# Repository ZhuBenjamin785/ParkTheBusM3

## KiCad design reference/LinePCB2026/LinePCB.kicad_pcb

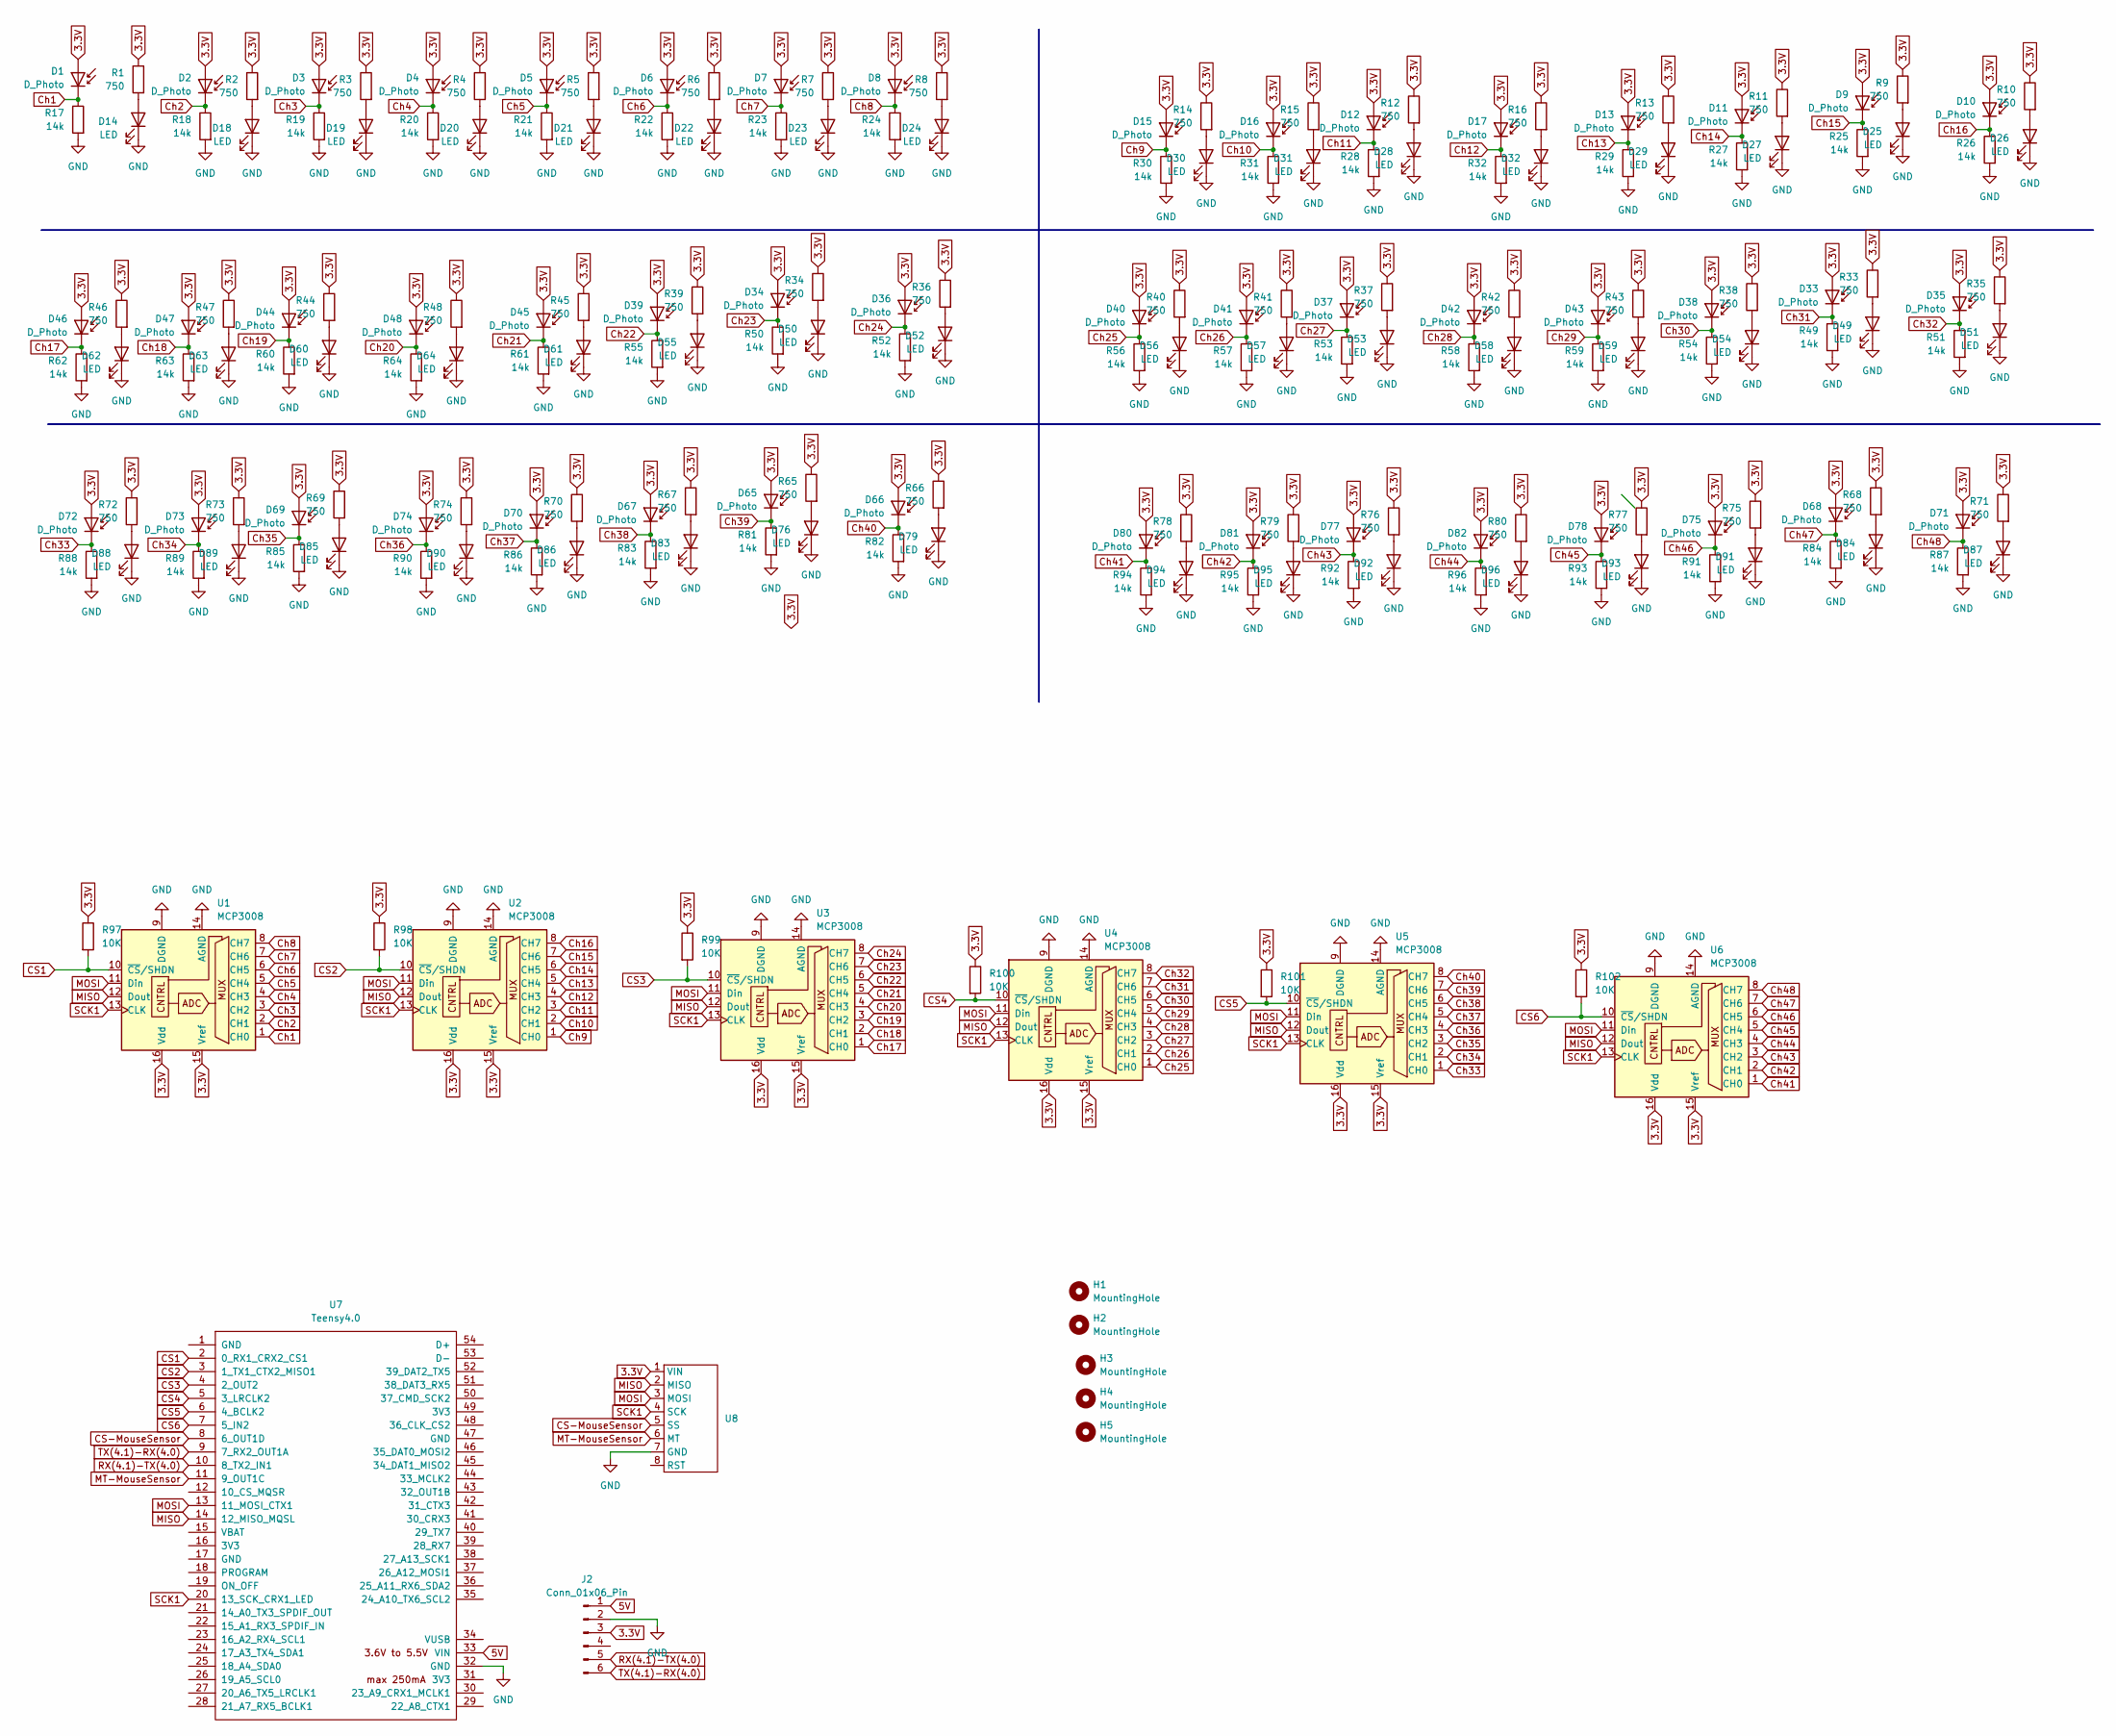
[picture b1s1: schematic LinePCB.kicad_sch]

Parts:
D1, D2, D3, D4, D5, D6, D7, D8, D9, D10, D11, D12, D13, D15, D16, D17, D33, D34, D35, D36, D37, D38, D39, D40, D41, D42, D43, D44, D45, D46, D47, D48, D65, D66, D67, D68, D69, D70, D71, D72, D73, D74, D75, D77, D78, D80, D81, D82: D_Photo; D_0805_2012Metric_Pad1.15x1.40mm_HandSolder
D14, D18, D19, D20, D21, D22, D23, D24, D25, D26, D27, D28, D29, D30, D31, D32, D49, D50, D51, D52, D53, D54, D55, D56, D57, D58, D59, D60, D61, D62, D63, D64, D76, D79, D83, D84, D85, D86, D87, D88, D89, D90, D91, D92, D93, D94, D95, D96: LED; LED_0805_2012Metric_Pad1.15x1.40mm_HandSolder
H1, H2, H3, H4, H5: MountingHole; MountingHole_3.2mm_M3_DIN965_Pad
J2: Conn_01x06_Pin; JST_XH_B6B-XH-A_1x06_P2.50mm_Vertical
R1, R2, R3, R4, R5, R6, R7, R8, R9, R10, R11, R12, R13, R14, R15, R16, R33, R34, R35, R36, R37, R38, R39, R40, R41, R42, R43, R44, R45, R46, R47, R48, R65, R66, R67, R68, R69, R70, R71, R72, R73, R74, R75, R76, R77, R78, R79, R80: 750; R_0805_2012Metric_Pad1.20x1.40mm_HandSolder
R17, R18, R19, R20, R21, R22, R23, R24, R25, R26, R27, R28, R29, R30, R31, R32, R49, R50, R51, R52, R53, R54, R55, R56, R57, R58, R59, R60, R61, R62, R63, R64, R81, R82, R83, R84, R85, R86, R87, R88, R89, R90, R91, R92, R93, R94, R95, R96: 14k; R_0805_2012Metric_Pad1.20x1.40mm_HandSolder
R97, R98, R99, R100, R101, R102: 10K; R_0805_2012Metric_Pad1.20x1.40mm_HandSolder
U1, U2, U3, U4, U5, U6: MCP3008; SOIC16-N_MC_MCH-L
U7: Teensy4.0; Teensy40
U8: JST_XH_B8B-XH-A_1x08_P2.50mm_Vertical

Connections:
3.3V: D1.2 (A), D2.2 (A), D3.2 (A), D4.2 (A), D5.2 (A), D6.2 (A), D7.2 (A), D8.2 (A), D9.2 (A), D10.2 (A), D11.2 (A), D12.2 (A), D13.2 (A), D15.2 (A), D16.2 (A), D17.2 (A), D33.2 (A), D34.2 (A), D35.2 (A), D36.2 (A), D37.2 (A), D38.2 (A), D39.2 (A), D40.2 (A), D41.2 (A), D42.2 (A), D43.2 (A), D44.2 (A), D45.2 (A), D46.2 (A), D47.2 (A), D48.2 (A), D65.2 (A), D66.2 (A), D67.2 (A), D68.2 (A), D69.2 (A), D70.2 (A), D71.2 (A), D72.2 (A), D73.2 (A), D74.2 (A), D75.2 (A), D77.2 (A), D78.2 (A), D80.2 (A), D81.2 (A), D82.2 (A), J2.3, R1.1, R2.1, R3.1, R4.1, R5.1, R6.1, R7.1, R8.1, R9.1, R10.1, R11.1, R12.1, R13.1, R14.1, R15.1, R16.1, R33.1, R34.1, R35.1, R36.1, R37.1, R38.1, R39.1, R40.1, R41.1, R42.1, R43.1, R44.1, R45.1, R46.1, R47.1, R48.1, R65.1, R66.1, R67.1, R68.1, R69.1, R70.1, R71.1, R72.1, R73.1, R74.1, R75.1, R76.1, R77.1, R78.1, R79.1, R80.1, R97.1, R98.1, R99.1, R100.1, R101.1, R102.1, U1.15 (Vref), U1.16 (Vdd), U2.15 (Vref), U2.16 (Vdd), U3.15 (Vref), U3.16 (Vdd), U4.15 (Vref), U4.16 (Vdd), U5.15 (Vref), U5.16 (Vdd), U6.15 (Vref), U6.16 (Vdd), U8.1 (VIN)
5V: J2.1, U7.33 (VIN)
CS1: R97.2, U1.10 (~CS/SHDN), U7.2 (0_RX1_CRX2_CS1)
CS2: R98.2, U2.10 (~CS/SHDN), U7.3 (1_TX1_CTX2_MISO1)
CS3: R99.2, U3.10 (~CS/SHDN), U7.4 (2_OUT2)
CS4: R100.2, U4.10 (~CS/SHDN), U7.5 (3_LRCLK2)
CS5: R101.2, U5.10 (~CS/SHDN), U7.6 (4_BCLK2)
CS6: R102.2, U6.10 (~CS/SHDN), U7.7 (5_IN2)
CS-MouseSensor: U7.8 (6_OUT1D), U8.5 (SS)
Ch1: D1.1 (K), R17.1, U1.1 (CH0)
Ch2: D2.1 (K), R18.1, U1.2 (CH1)
Ch3: D3.1 (K), R19.1, U1.3 (CH2)
Ch4: D4.1 (K), R20.1, U1.4 (CH3)
Ch5: D5.1 (K), R21.1, U1.5 (CH4)
Ch6: D6.1 (K), R22.1, U1.6 (CH5)
Ch7: D7.1 (K), R23.1, U1.7 (CH6)
Ch8: D8.1 (K), R24.1, U1.8 (CH7)
Ch9: D15.1 (K), R30.1, U2.1 (CH0)
Ch10: D16.1 (K), R31.1, U2.2 (CH1)
Ch11: D12.1 (K), R28.1, U2.3 (CH2)
Ch12: D17.1 (K), R32.1, U2.4 (CH3)
Ch13: D13.1 (K), R29.1, U2.5 (CH4)
Ch14: D11.1 (K), R27.1, U2.6 (CH5)
Ch15: D9.1 (K), R25.1, U2.7 (CH6)
Ch16: D10.1 (K), R26.1, U2.8 (CH7)
Ch17: D46.1 (K), R62.1, U3.1 (CH0)
Ch18: D47.1 (K), R63.1, U3.2 (CH1)
Ch19: D44.1 (K), R60.1, U3.3 (CH2)
Ch20: D48.1 (K), R64.1, U3.4 (CH3)
Ch21: D45.1 (K), R61.1, U3.5 (CH4)
Ch22: D39.1 (K), R55.1, U3.6 (CH5)
Ch23: D34.1 (K), R50.1, U3.7 (CH6)
Ch24: D36.1 (K), R52.1, U3.8 (CH7)
Ch25: D40.1 (K), R56.1, U4.1 (CH0)
Ch26: D41.1 (K), R57.1, U4.2 (CH1)
Ch27: D37.1 (K), R53.1, U4.3 (CH2)
Ch28: D42.1 (K), R58.1, U4.4 (CH3)
Ch29: D43.1 (K), R59.1, U4.5 (CH4)
Ch30: D38.1 (K), R54.1, U4.6 (CH5)
Ch31: D33.1 (K), R49.1, U4.7 (CH6)
Ch32: D35.1 (K), R51.1, U4.8 (CH7)
Ch33: D72.1 (K), R88.1, U5.1 (CH0)
Ch34: D73.1 (K), R89.1, U5.2 (CH1)
Ch35: D69.1 (K), R85.1, U5.3 (CH2)
Ch36: D74.1 (K), R90.1, U5.4 (CH3)
Ch37: D70.1 (K), R86.1, U5.5 (CH4)
Ch38: D67.1 (K), R83.1, U5.6 (CH5)
Ch39: D65.1 (K), R81.1, U5.7 (CH6)
Ch40: D66.1 (K), R82.1, U5.8 (CH7)
Ch41: D80.1 (K), R94.1, U6.1 (CH0)
Ch42: D81.1 (K), R95.1, U6.2 (CH1)
Ch43: D77.1 (K), R92.1, U6.3 (CH2)
Ch44: D82.1 (K), R96.1, U6.4 (CH3)
Ch45: D78.1 (K), R93.1, U6.5 (CH4)
Ch46: D75.1 (K), R91.1, U6.6 (CH5)
Ch47: D68.1 (K), R84.1, U6.7 (CH6)
Ch48: D71.1 (K), R87.1, U6.8 (CH7)
GND: D14.1 (K), D18.1 (K), D19.1 (K), D20.1 (K), D21.1 (K), D22.1 (K), D23.1 (K), D24.1 (K), D25.1 (K), D26.1 (K), D27.1 (K), D28.1 (K), D29.1 (K), D30.1 (K), D31.1 (K), D32.1 (K), D49.1 (K), D50.1 (K), D51.1 (K), D52.1 (K), D53.1 (K), D54.1 (K), D55.1 (K), D56.1 (K), D57.1 (K), D58.1 (K), D59.1 (K), D60.1 (K), D61.1 (K), D62.1 (K), D63.1 (K), D64.1 (K), D76.1 (K), D79.1 (K), D83.1 (K), D84.1 (K), D85.1 (K), D86.1 (K), D87.1 (K), D88.1 (K), D89.1 (K), D90.1 (K), D91.1 (K), D92.1 (K), D93.1 (K), D94.1 (K), D95.1 (K), D96.1 (K), J2.2, R17.2, R18.2, R19.2, R20.2, R21.2, R22.2, R23.2, R24.2, R25.2, R26.2, R27.2, R28.2, R29.2, R30.2, R31.2, R32.2, R49.2, R50.2, R51.2, R52.2, R53.2, R54.2, R55.2, R56.2, R57.2, R58.2, R59.2, R60.2, R61.2, R62.2, R63.2, R64.2, R81.2, R82.2, R83.2, R84.2, R85.2, R86.2, R87.2, R88.2, R89.2, R90.2, R91.2, R92.2, R93.2, R94.2, R95.2, R96.2, U1.9 (DGND), U1.14 (AGND), U2.9 (DGND), U2.14 (AGND), U3.9 (DGND), U3.14 (AGND), U4.9 (DGND), U4.14 (AGND), U5.9 (DGND), U5.14 (AGND), U6.9 (DGND), U6.14 (AGND), U7.32 (GND), U8.7 (GND)
MISO: U1.12 (Dout), U2.12 (Dout), U3.12 (Dout), U4.12 (Dout), U5.12 (Dout), U6.12 (Dout), U7.14 (12_MISO_MQSL), U8.2 (MISO)
MOSI: U1.11 (Din), U2.11 (Din), U3.11 (Din), U4.11 (Din), U5.11 (Din), U6.11 (Din), U7.13 (11_MOSI_CTX1), U8.3 (MOSI)
MT-MouseSensor: U7.11 (9_OUT1C), U8.6 (MT)
unnamed: D14.2 (A), R1.2
unnamed: D18.2 (A), R2.2
unnamed: D19.2 (A), R3.2
unnamed: D20.2 (A), R4.2
unnamed: D21.2 (A), R5.2
unnamed: D22.2 (A), R6.2
unnamed: D23.2 (A), R7.2
unnamed: D24.2 (A), R8.2
unnamed: D25.2 (A), R9.2
unnamed: D26.2 (A), R10.2
unnamed: D27.2 (A), R11.2
unnamed: D28.2 (A), R12.2
unnamed: D29.2 (A), R13.2
unnamed: D30.2 (A), R14.2
unnamed: D31.2 (A), R15.2
unnamed: D32.2 (A), R16.2
unnamed: D49.2 (A), R33.2
unnamed: D50.2 (A), R34.2
unnamed: D51.2 (A), R35.2
unnamed: D52.2 (A), R36.2
unnamed: D53.2 (A), R37.2
unnamed: D54.2 (A), R38.2
unnamed: D55.2 (A), R39.2
unnamed: D56.2 (A), R40.2
unnamed: D57.2 (A), R41.2
unnamed: D58.2 (A), R42.2
unnamed: D59.2 (A), R43.2
unnamed: D60.2 (A), R44.2
unnamed: D61.2 (A), R45.2
unnamed: D62.2 (A), R46.2
unnamed: D63.2 (A), R47.2
unnamed: D64.2 (A), R48.2
unnamed: D76.2 (A), R65.2
unnamed: D79.2 (A), R66.2
unnamed: D83.2 (A), R67.2
unnamed: D84.2 (A), R68.2
unnamed: D85.2 (A), R69.2
unnamed: D86.2 (A), R70.2
unnamed: D87.2 (A), R71.2
unnamed: D88.2 (A), R72.2
unnamed: D89.2 (A), R73.2
unnamed: D90.2 (A), R74.2
unnamed: D91.2 (A), R75.2
unnamed: D92.2 (A), R76.2
unnamed: D93.2 (A), R77.2
unnamed: D94.2 (A), R78.2
unnamed: D95.2 (A), R79.2
unnamed: D96.2 (A), R80.2
RX(4.1)-TX(4.0): J2.5, U7.10 (8_TX2_IN1)
SCK1: U1.13 (CLK), U2.13 (CLK), U3.13 (CLK), U4.13 (CLK), U5.13 (CLK), U6.13 (CLK), U7.20 (13_SCK_CRX1_LED), U8.4 (SCK)
TX(4.1)-RX(4.0): J2.6, U7.9 (7_RX2_OUT1A)

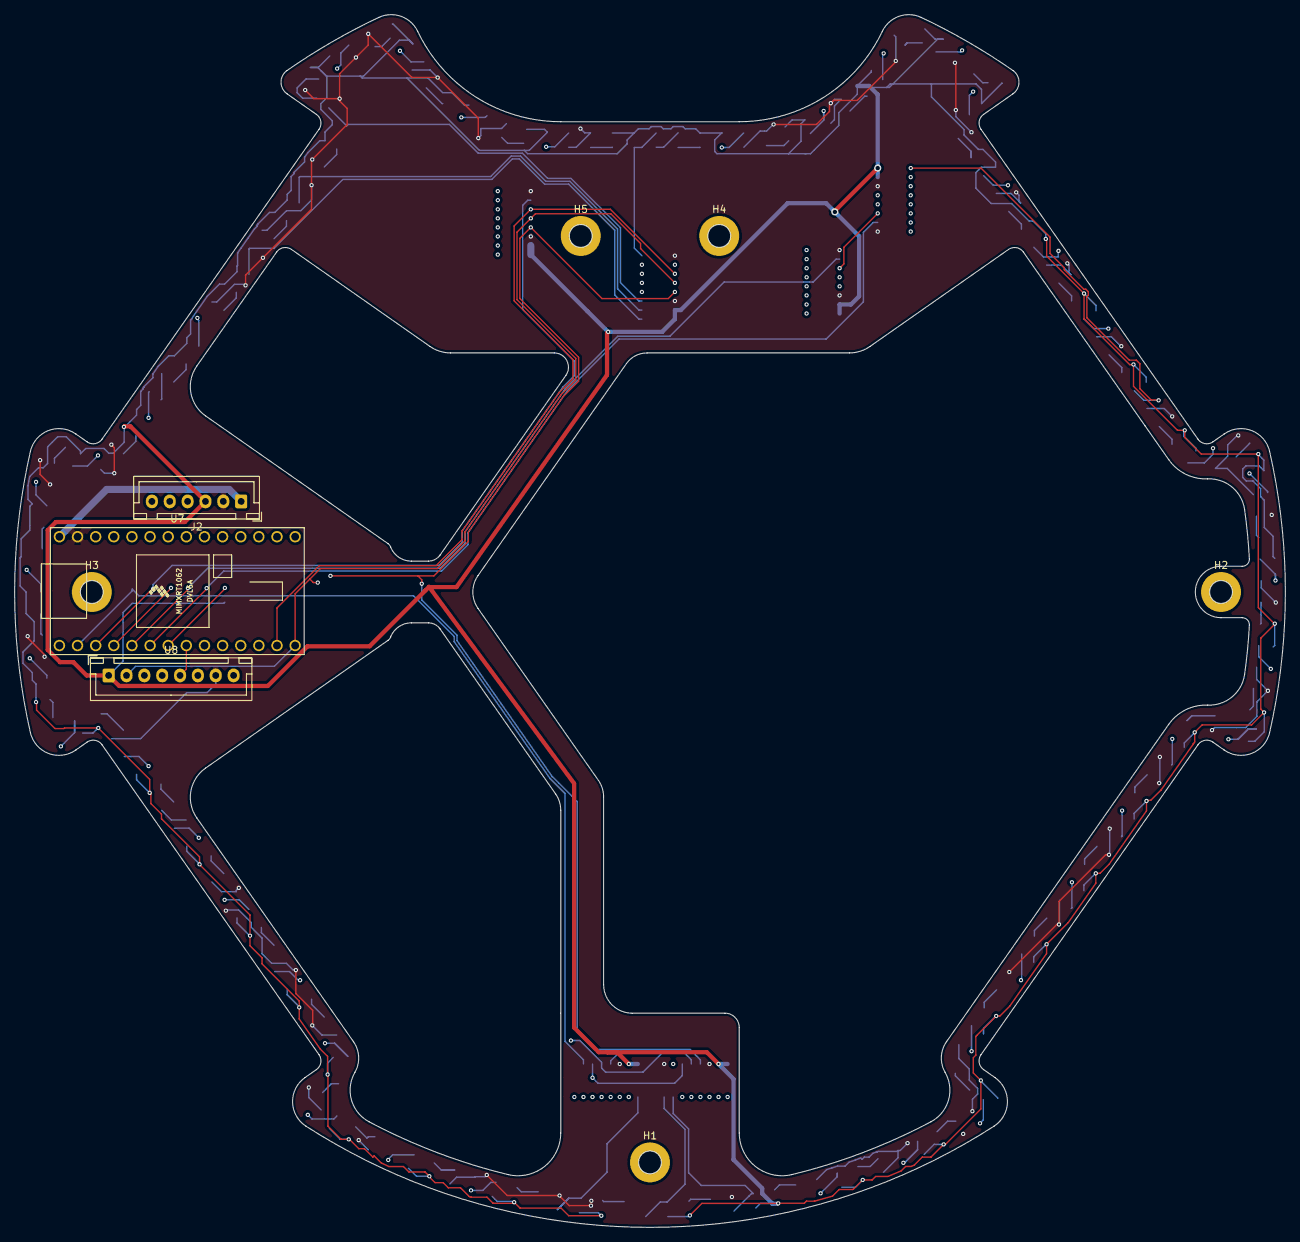
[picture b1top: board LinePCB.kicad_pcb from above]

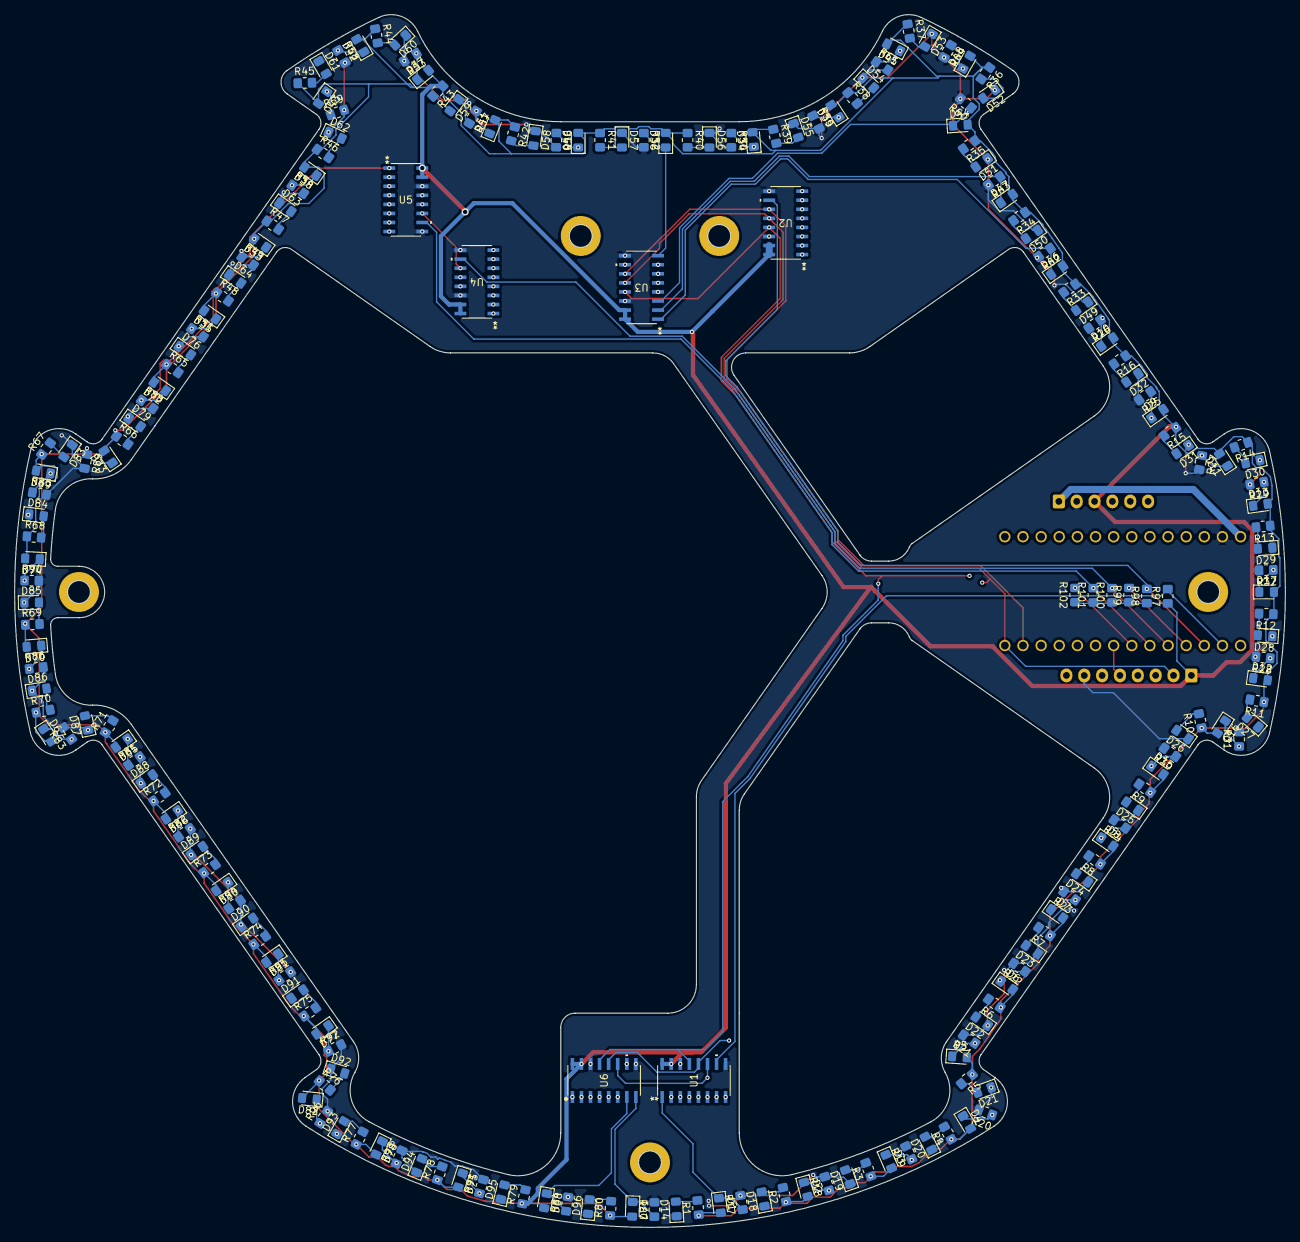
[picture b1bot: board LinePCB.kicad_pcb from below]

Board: 4 copper layers, 178.0 x 169.9 mm, 212 parts (204 on the bottom side), 112 nets.

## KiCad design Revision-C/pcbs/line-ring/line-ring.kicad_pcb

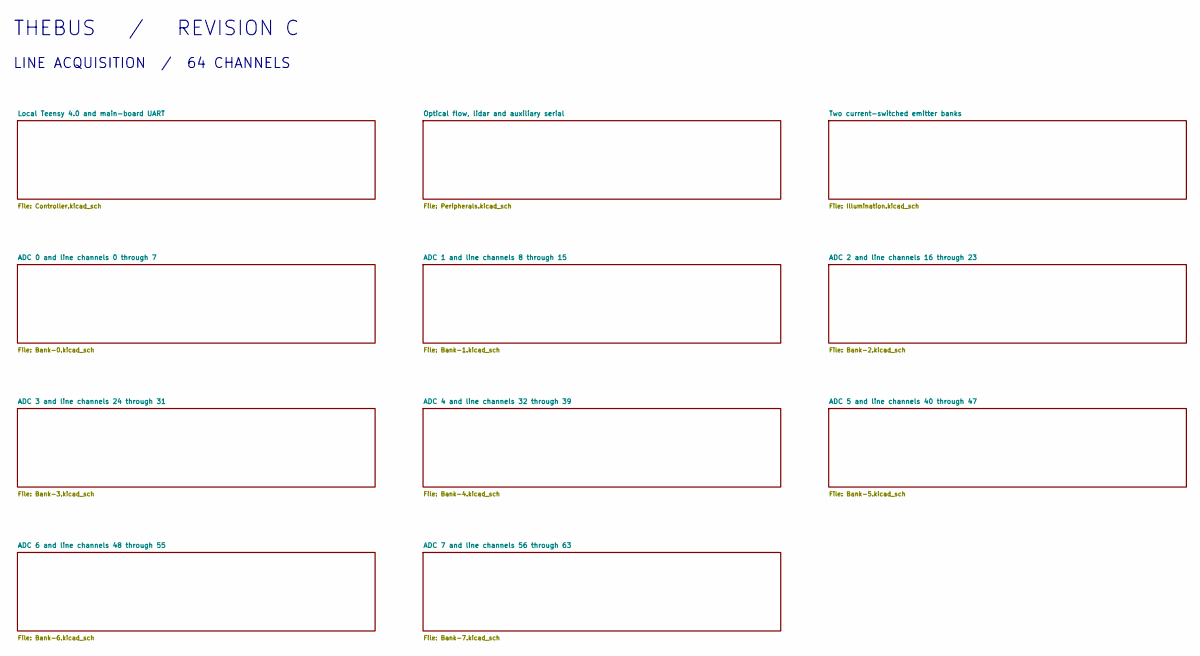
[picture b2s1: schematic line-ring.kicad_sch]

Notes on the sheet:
THEBUS / REVISION C
LINE ACQUISITION / 64 CHANNELS

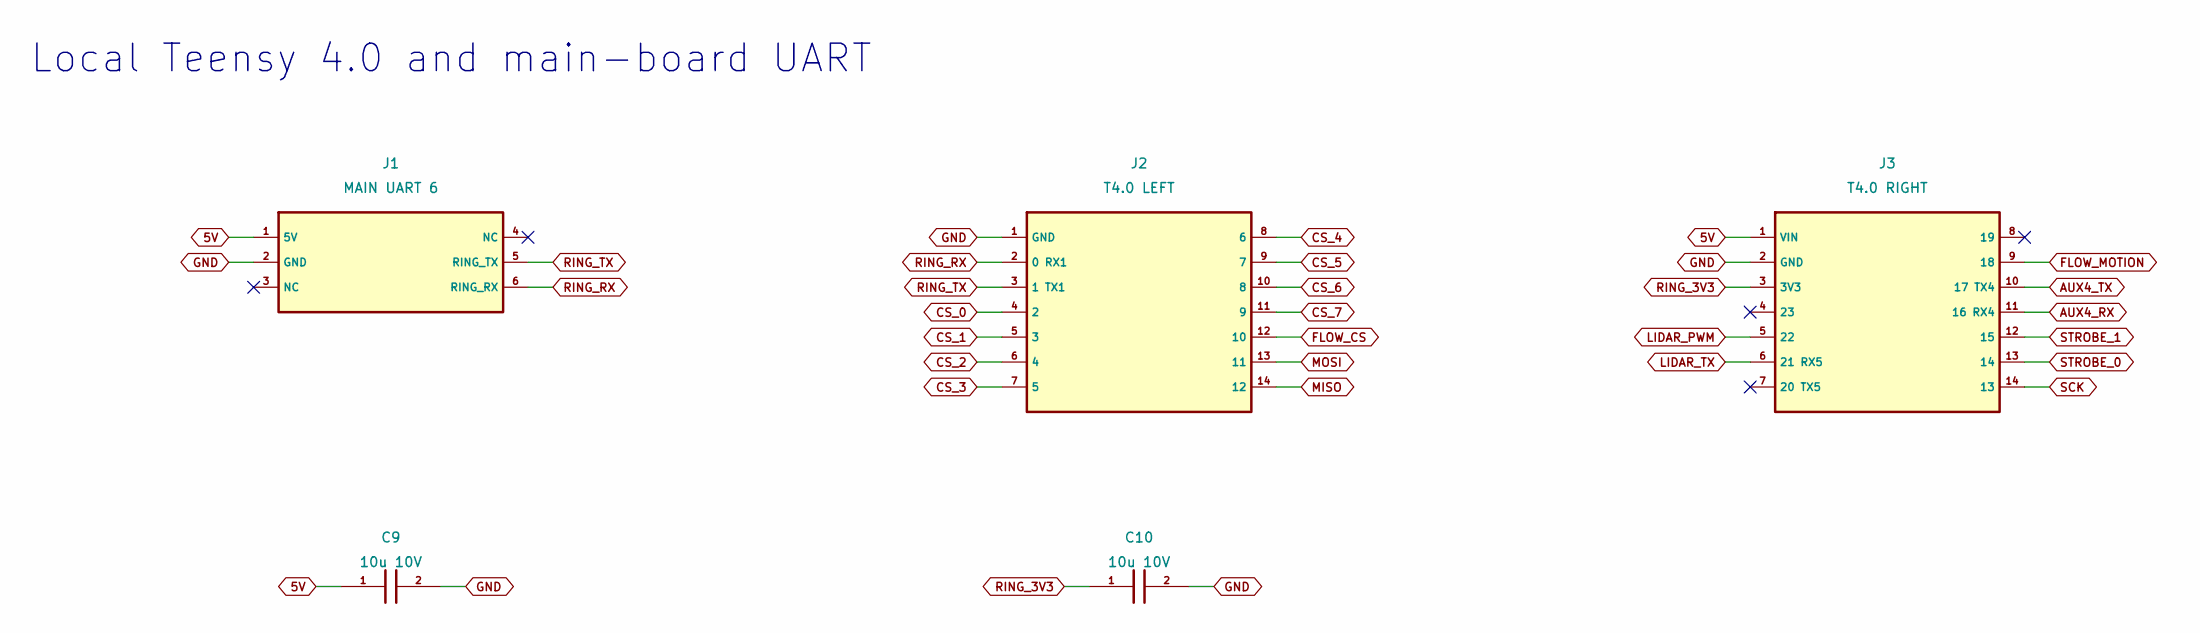
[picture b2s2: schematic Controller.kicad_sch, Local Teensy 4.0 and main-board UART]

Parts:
C9, C10: 10u 10V; C_0805_2012Metric
J1: MAIN UART 6; JST_XH_B6B-XH-A_1x06_P2.50mm_Vertical
J2: T4.0 LEFT; PinHeader_1x14_P2.54mm_Vertical
J3: T4.0 RIGHT; PinHeader_1x14_P2.54mm_Vertical

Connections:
5V: C9.1, J1.1 (5V), J3.1 (VIN); also elsewhere on the board
AUX4_RX: J3.11 (16 RX4); also elsewhere on the board
AUX4_TX: J3.10 (17 TX4); also elsewhere on the board
CS_0: J2.4 (2); also elsewhere on the board
CS_1: J2.5 (3); also elsewhere on the board
CS_2: J2.6 (4); also elsewhere on the board
CS_3: J2.7 (5); also elsewhere on the board
CS_4: J2.8 (6); also elsewhere on the board
CS_5: J2.9 (7); also elsewhere on the board
CS_6: J2.10 (8); also elsewhere on the board
CS_7: J2.11 (9); also elsewhere on the board
FLOW_CS: J2.12 (10); also elsewhere on the board
FLOW_MOTION: J3.9 (18); also elsewhere on the board
GND: C9.2, C10.2, J1.2 (GND), J2.1 (GND), J3.2 (GND); also elsewhere on the board
LIDAR_PWM: J3.5 (22); also elsewhere on the board
LIDAR_TX: J3.6 (21 RX5); also elsewhere on the board
MISO: J2.14 (12); also elsewhere on the board
MOSI: J2.13 (11); also elsewhere on the board
RING_3V3: C10.1, J3.3 (3V3); also elsewhere on the board
RING_RX: J1.6 (RING_RX), J2.2 (0 RX1)
RING_TX: J1.5 (RING_TX), J2.3 (1 TX1)
SCK: J3.14 (13); also elsewhere on the board
STROBE_0: J3.13 (14); also elsewhere on the board
STROBE_1: J3.12 (15); also elsewhere on the board

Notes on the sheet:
Local Teensy 4.0 and main-board UART

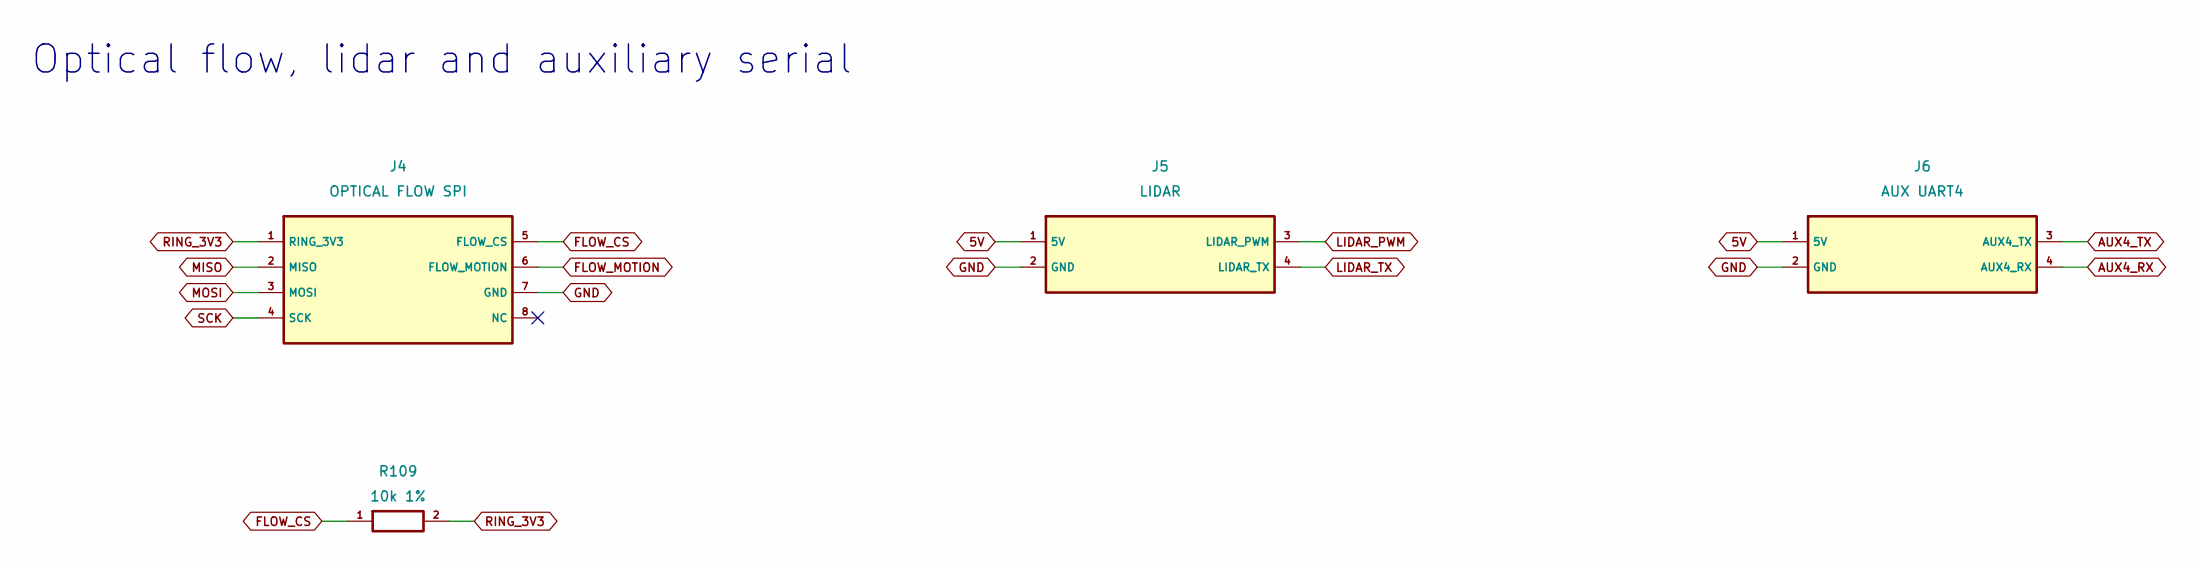
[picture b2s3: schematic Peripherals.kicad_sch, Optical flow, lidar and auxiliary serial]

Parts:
J4: OPTICAL FLOW SPI; JST_XH_B8B-XH-A_1x08_P2.50mm_Vertical
J5: LIDAR; JST_XH_B4B-XH-A_1x04_P2.50mm_Vertical
J6: AUX UART4; JST_XH_B4B-XH-A_1x04_P2.50mm_Vertical
R109: 10k 1%; R_0805_2012Metric

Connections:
5V: J5.1 (5V), J6.1 (5V); also elsewhere on the board
AUX4_RX: J6.4 (AUX4_RX); also elsewhere on the board
AUX4_TX: J6.3 (AUX4_TX); also elsewhere on the board
FLOW_CS: J4.5 (FLOW_CS), R109.1; also elsewhere on the board
FLOW_MOTION: J4.6 (FLOW_MOTION); also elsewhere on the board
GND: J4.7 (GND), J5.2 (GND), J6.2 (GND); also elsewhere on the board
LIDAR_PWM: J5.3 (LIDAR_PWM); also elsewhere on the board
LIDAR_TX: J5.4 (LIDAR_TX); also elsewhere on the board
MISO: J4.2 (MISO); also elsewhere on the board
MOSI: J4.3 (MOSI); also elsewhere on the board
RING_3V3: J4.1 (RING_3V3), R109.2; also elsewhere on the board
SCK: J4.4 (SCK); also elsewhere on the board

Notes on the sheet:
Optical flow, lidar and auxiliary serial

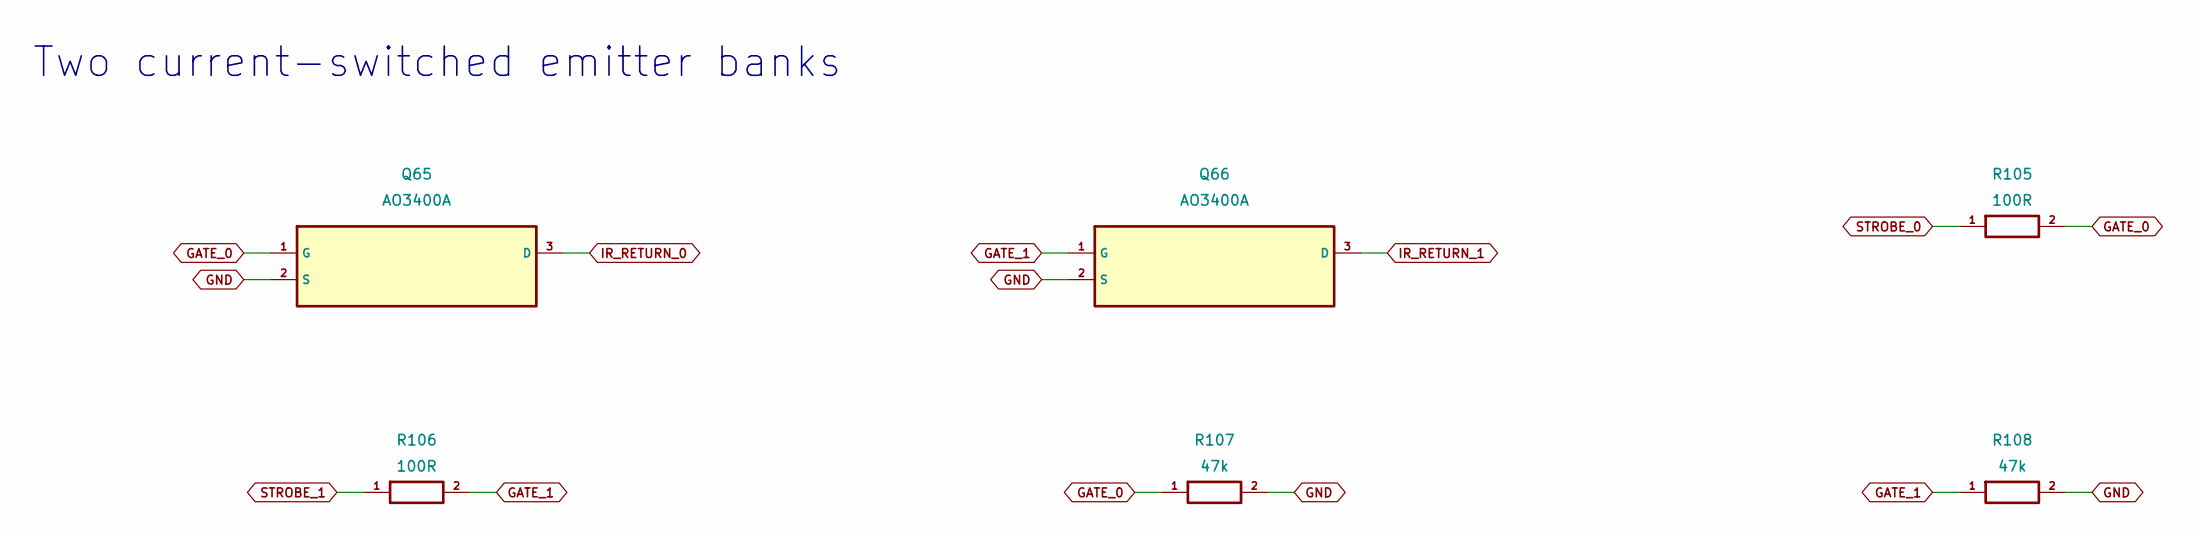
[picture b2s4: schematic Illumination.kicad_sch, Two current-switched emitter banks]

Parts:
Q65, Q66: AO3400A; SOT-23
R105, R106: 100R; R_0805_2012Metric
R107, R108: 47k; R_0805_2012Metric

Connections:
GATE_0: Q65.1 (G), R105.2, R107.1
GATE_1: Q66.1 (G), R106.2, R108.1
GND: Q65.2 (S), Q66.2 (S), R107.2, R108.2; also elsewhere on the board
IR_RETURN_0: Q65.3 (D); also elsewhere on the board
IR_RETURN_1: Q66.3 (D); also elsewhere on the board
STROBE_0: R105.1; also elsewhere on the board
STROBE_1: R106.1; also elsewhere on the board

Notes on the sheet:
Two current-switched emitter banks

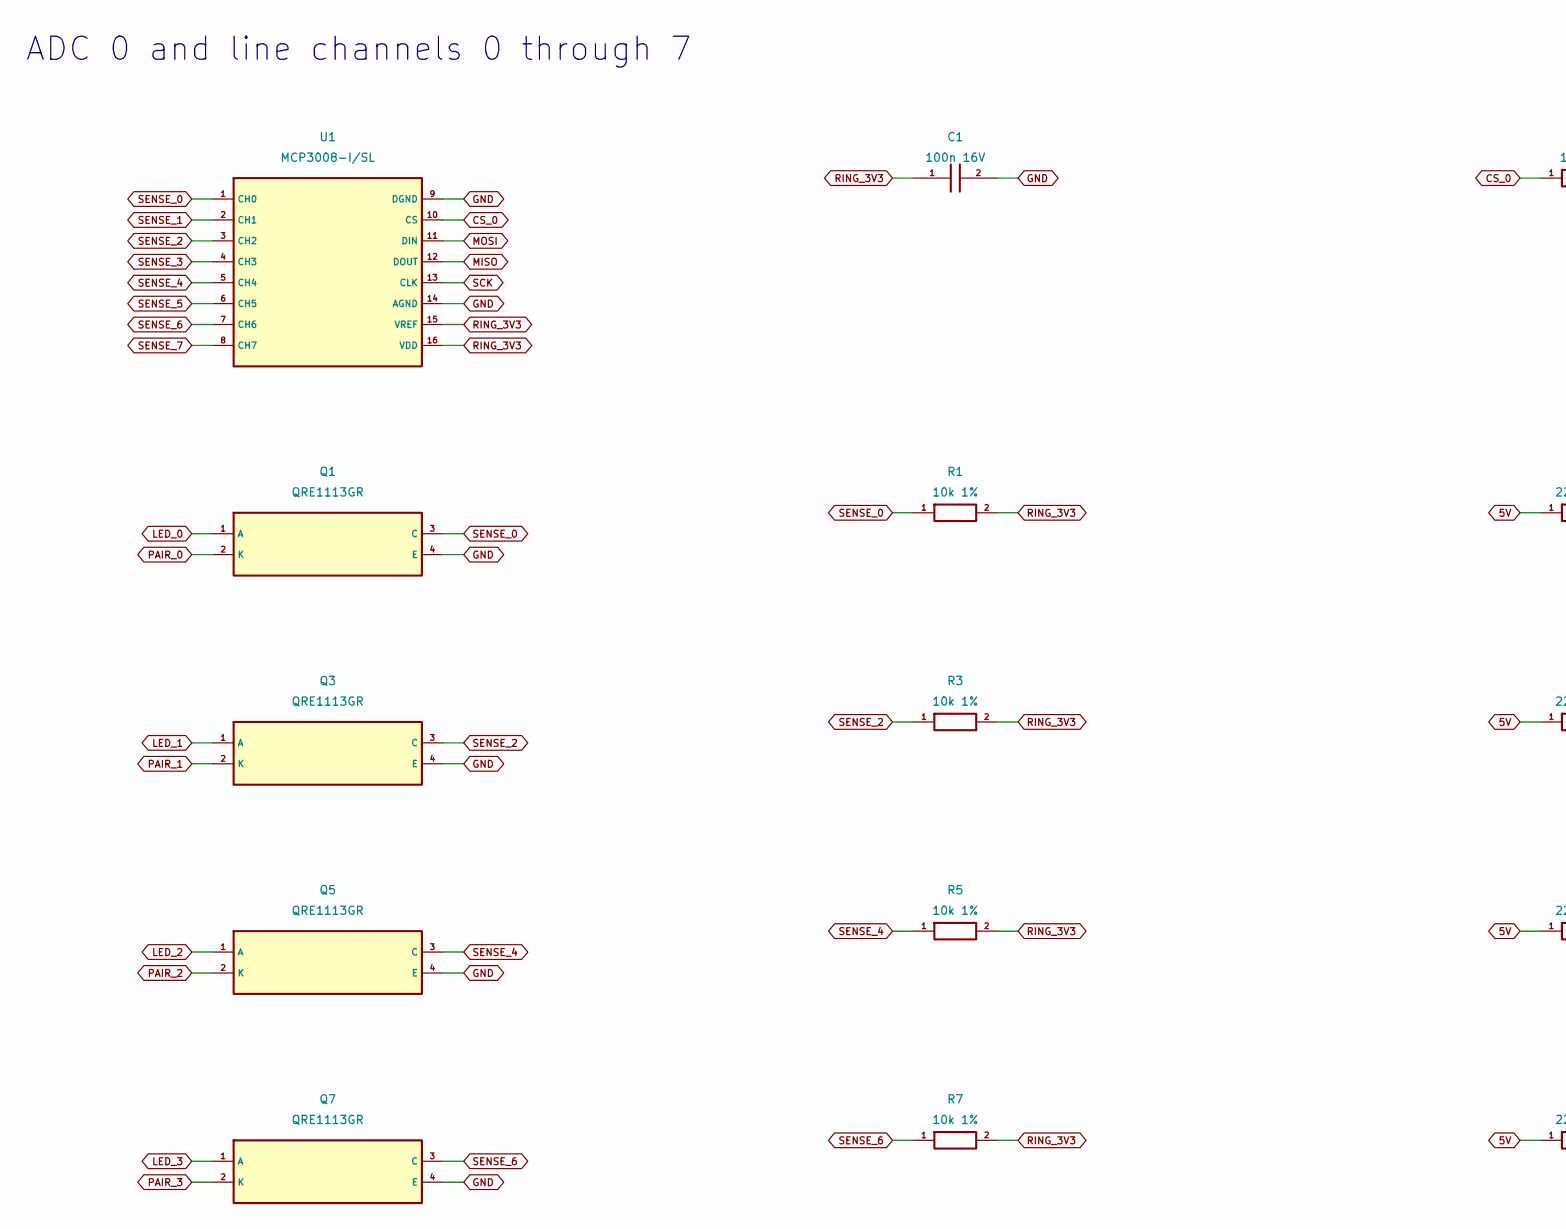
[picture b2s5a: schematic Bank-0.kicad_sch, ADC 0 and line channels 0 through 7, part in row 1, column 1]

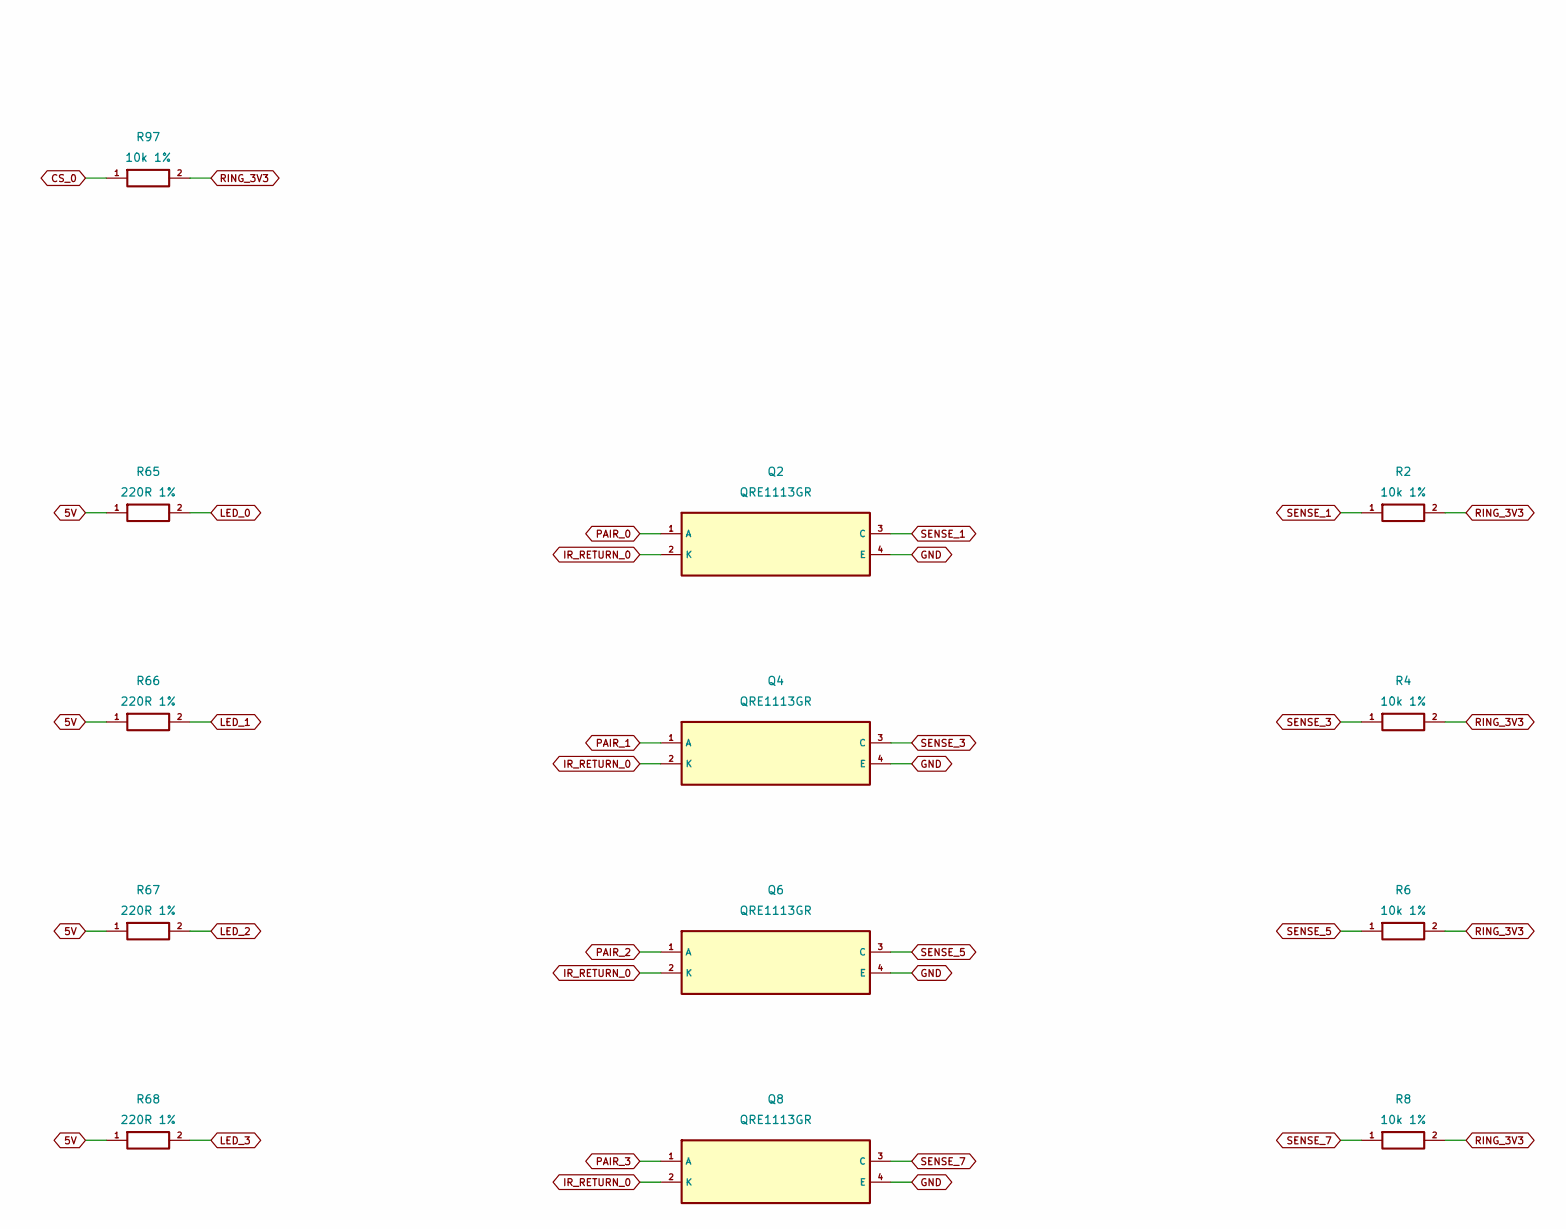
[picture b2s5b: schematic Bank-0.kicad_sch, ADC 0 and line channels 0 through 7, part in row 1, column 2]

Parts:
C1: 100n 16V; C_0805_2012Metric
Q1, Q2, Q3, Q4, Q5, Q6, Q7, Q8: QRE1113GR; OnSemi_CASE100CY
R1, R2, R3, R4, R5, R6, R7, R8, R97: 10k 1%; R_0805_2012Metric
R65, R66, R67, R68: 220R 1%; R_0805_2012Metric
U1: MCP3008-I/SL; SOIC-16_3.9x9.9mm_P1.27mm

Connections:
5V: R65.1, R66.1, R67.1, R68.1; also elsewhere on the board
CS_0: R97.1, U1.10 (CS); also elsewhere on the board
GND: C1.2, Q1.4 (E), Q2.4 (E), Q3.4 (E), Q4.4 (E), Q5.4 (E), Q6.4 (E), Q7.4 (E), Q8.4 (E), U1.9 (DGND), U1.14 (AGND); also elsewhere on the board
IR_RETURN_0: Q2.2 (K), Q4.2 (K), Q6.2 (K), Q8.2 (K); also elsewhere on the board
LED_0: Q1.1 (A), R65.2
LED_1: Q3.1 (A), R66.2
LED_2: Q5.1 (A), R67.2
LED_3: Q7.1 (A), R68.2
MISO: U1.12 (DOUT); also elsewhere on the board
MOSI: U1.11 (DIN); also elsewhere on the board
PAIR_0: Q1.2 (K), Q2.1 (A)
PAIR_1: Q3.2 (K), Q4.1 (A)
PAIR_2: Q5.2 (K), Q6.1 (A)
PAIR_3: Q7.2 (K), Q8.1 (A)
RING_3V3: C1.1, R1.2, R2.2, R3.2, R4.2, R5.2, R6.2, R7.2, R8.2, R97.2, U1.15 (VREF), U1.16 (VDD); also elsewhere on the board
SCK: U1.13 (CLK); also elsewhere on the board
SENSE_0: Q1.3 (C), R1.1, U1.1 (CH0)
SENSE_1: Q2.3 (C), R2.1, U1.2 (CH1)
SENSE_2: Q3.3 (C), R3.1, U1.3 (CH2)
SENSE_3: Q4.3 (C), R4.1, U1.4 (CH3)
SENSE_4: Q5.3 (C), R5.1, U1.5 (CH4)
SENSE_5: Q6.3 (C), R6.1, U1.6 (CH5)
SENSE_6: Q7.3 (C), R7.1, U1.7 (CH6)
SENSE_7: Q8.3 (C), R8.1, U1.8 (CH7)

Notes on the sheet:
ADC 0 and line channels 0 through 7
